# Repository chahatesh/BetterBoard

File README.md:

# BetterBoard

BetterBoard is a custom PCB I designed in KiCad. This repo contains the PCB design, schematics, and manufacturing files.

Betterboard is designed to operate efficiently on battery power and includes several debug LEDs. I created it because many of my projects rely on batteries, and troubleshooting them is often a major pain.

## USB Data Line Problem

One problem I ran into was routing the USB D+ and D- data lines. The connections crossed, which made it tricky to route the traces without interfering with each other.

## Finished PCB Design

After working through the routing issues, I finished the PCB layout. Here's the final design in KiCad.

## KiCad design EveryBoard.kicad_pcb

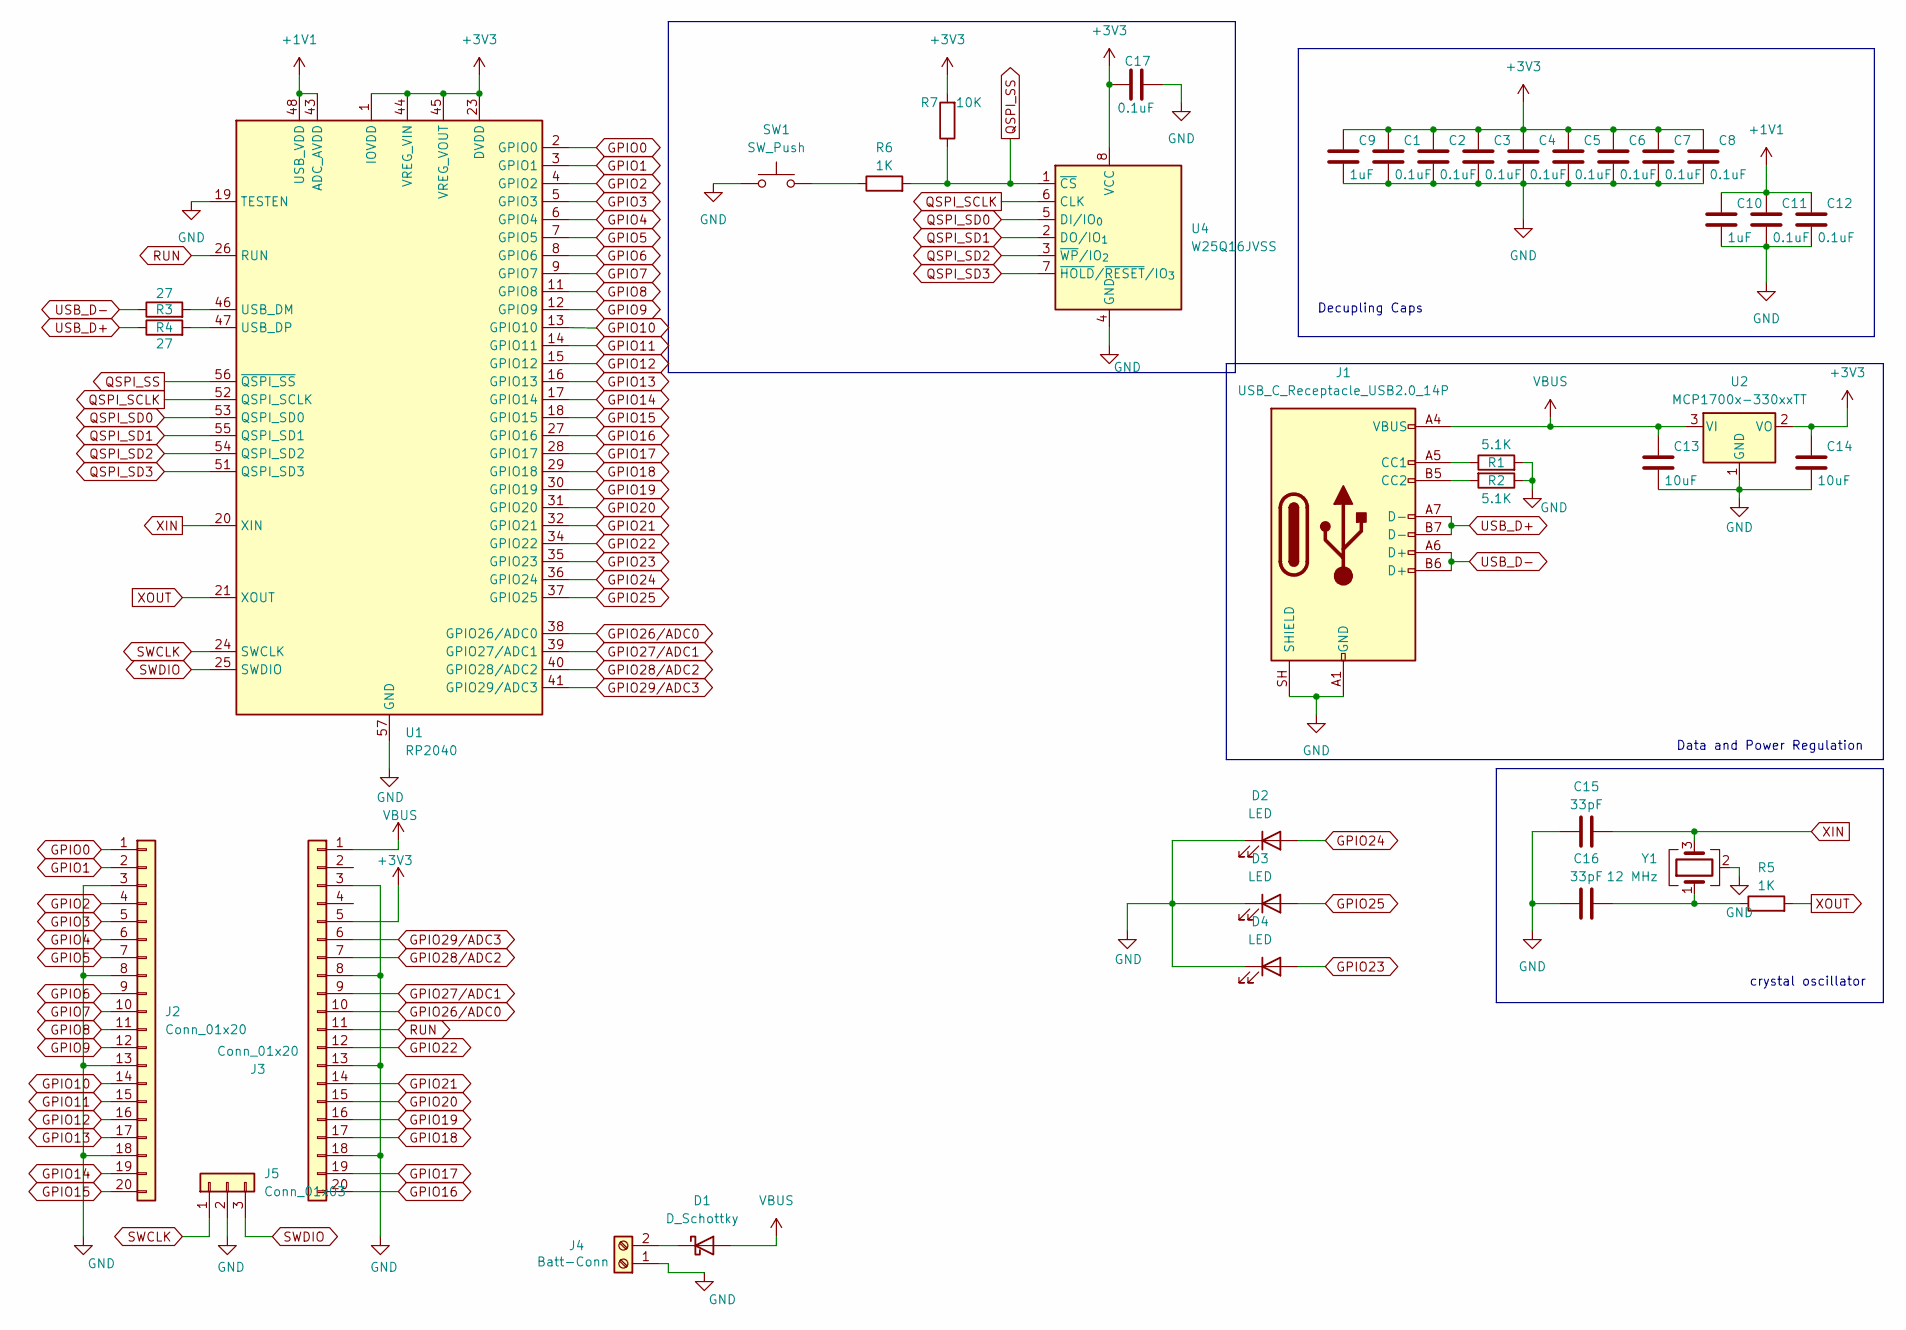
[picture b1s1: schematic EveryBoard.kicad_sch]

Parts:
C1, C2, C3, C4, C5, C6, C7, C8, C11, C12, C17: 0.1uF; C_0402_1005Metric
C9, C10: 1uF; C_0402_1005Metric
C13, C14: 10uF; C_0603_1608Metric
C15, C16: 33pF; C_0402_1005Metric
D1: D_Schottky; D_SOD-123
D2, D3, D4: LED; LED_0603_1608Metric
J1: USB_C_Receptacle_USB2.0_14P; USB_C_Receptacle_HRO_TYPE-C-31-M-12
J2, J3: Conn_01x20; PinHeader_1x20_P2.54mm_Vertical
J4: Batt-Conn; PinSocket_1x02_P2.54mm_Vertical
J5: Conn_01x03; PinHeader_1x03_P2.54mm_Vertical
R1, R2: 5.1K; R_0402_1005Metric
R3, R4: 27; R_0402_1005Metric
R5, R6: 1K; R_0402_1005Metric
R7: 10K; R_0402_1005Metric
SW1: SW_Push; SW_Push_SPST_NO_Alps_SKRK
U1: RP2040; QFN-56-1EP_7x7mm_P0.4mm_EP3.2x3.2mm
U2: MCP1700x-330xxTT; SOT-23
U4: W25Q16JVSS; Winbond_USON-8-1EP_3x2mm_P0.5mm_EP0.2x1.6mm
Y1: 12 MHz; Crystal_SMD_3225-4Pin_3.2x2.5mm

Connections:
+1V1: C10.1, C11.1, C12.1, U1.43 (ADC_AVDD), U1.48 (USB_VDD)
+3V3: C1.1, C2.1, C3.1, C4.1, C5.1, C6.1, C7.1, C8.1, C9.1, C14.1, C17.2, J3.5, R7.2, U1.1 (IOVDD), U1.10 (IOVDD), U1.22 (IOVDD), U1.23 (DVDD), U1.33 (IOVDD), U1.42 (IOVDD), U1.44 (VREG_VIN), U1.45 (VREG_VOUT), U1.49 (IOVDD), U1.50 (DVDD), U2.2 (VO), U4.8 (VCC)
GND: C1.2, C2.2, C3.2, C4.2, C5.2, C6.2, C7.2, C8.2, C9.2, C10.2, C11.2, C12.2, C13.2, C14.2, C15.1, C16.1, C17.1, D2.1 (K), D3.1 (K), D4.1 (K), J1.A1 (GND), J1.A12 (GND), J1.B1 (GND), J1.B12 (GND), J1.SH (SHIELD), J2.3, J2.8, J2.13, J2.18, J3.3, J3.8, J3.13, J3.18, J4.1, J5.2, R1.2, R2.1, SW1.1, U1.19 (TESTEN), U1.57 (GND), U2.1 (GND), U4.4 (GND), Y1.2 (G), Y1.4 (G)
GPIO0: J2.1, U1.2 (GPIO0)
GPIO1: J2.2, U1.3 (GPIO1)
GPIO2: J2.4, U1.4 (GPIO2)
GPIO3: J2.5, U1.5 (GPIO3)
GPIO4: J2.6, U1.6 (GPIO4)
GPIO5: J2.7, U1.7 (GPIO5)
GPIO6: J2.9, U1.8 (GPIO6)
GPIO7: J2.10, U1.9 (GPIO7)
GPIO8: J2.11, U1.11 (GPIO8)
GPIO9: J2.12, U1.12 (GPIO9)
GPIO10: J2.14, U1.13 (GPIO10)
GPIO11: J2.15, U1.14 (GPIO11)
GPIO12: J2.16, U1.15 (GPIO12)
GPIO13: J2.17, U1.16 (GPIO13)
GPIO14: J2.19, U1.17 (GPIO14)
GPIO15: J2.20, U1.18 (GPIO15)
GPIO16: J3.20, U1.27 (GPIO16)
GPIO17: J3.19, U1.28 (GPIO17)
GPIO18: J3.17, U1.29 (GPIO18)
GPIO19: J3.16, U1.30 (GPIO19)
GPIO20: J3.15, U1.31 (GPIO20)
GPIO21: J3.14, U1.32 (GPIO21)
GPIO22: J3.12, U1.34 (GPIO22)
GPIO23: D4.2 (A), U1.35 (GPIO23)
GPIO24: D2.2 (A), U1.36 (GPIO24)
GPIO25: D3.2 (A), U1.37 (GPIO25)
GPIO26/ADC0: J3.10, U1.38 (GPIO26/ADC0)
GPIO27/ADC1: J3.9, U1.39 (GPIO27/ADC1)
GPIO28/ADC2: J3.7, U1.40 (GPIO28/ADC2)
GPIO29/ADC3: J3.6, U1.41 (GPIO29/ADC3)
unnamed: C16.2, R5.1, Y1.1
unnamed: D1.1 (K), J4.2
unnamed: J1.A5 (CC1), R1.1
unnamed: J1.B5 (CC2), R2.2
unnamed: R6.1, SW1.2
unnamed: R3.2, U1.46 (USB_DM)
unnamed: R4.2, U1.47 (USB_DP)
QSPI_SCLK: U1.52 (QSPI_SCLK), U4.6 (CLK)
QSPI_SD0: U1.53 (QSPI_SD0), U4.5 (DI/IO_{0})
QSPI_SD1: U1.55 (QSPI_SD1), U4.2 (DO/IO_{1})
QSPI_SD2: U1.54 (QSPI_SD2), U4.3 (~WP/IO_{2})
QSPI_SD3: U1.51 (QSPI_SD3), U4.7 (~HOLD/~RESET/IO_{3})
QSPI_SS: R6.2, R7.1, U1.56 (~QSPI_SS), U4.1 (~CS)
RUN: J3.11, U1.26 (RUN)
SWCLK: J5.1, U1.24 (SWCLK)
SWDIO: J5.3, U1.25 (SWDIO)
USB_D+: J1.A7 (D-), J1.B7 (D-), R4.1
USB_D-: J1.A6 (D+), J1.B6 (D+), R3.1
VBUS: C13.1, D1.2 (A), J1.A4 (VBUS), J1.A9 (VBUS), J1.B4 (VBUS), J1.B9 (VBUS), J3.1, U2.3 (VI)
XIN: C15.2, U1.20 (XIN), Y1.3
XOUT: R5.2, U1.21 (XOUT)

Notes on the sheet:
Decupling Caps
crystal oscillator
Data and Power Regulation

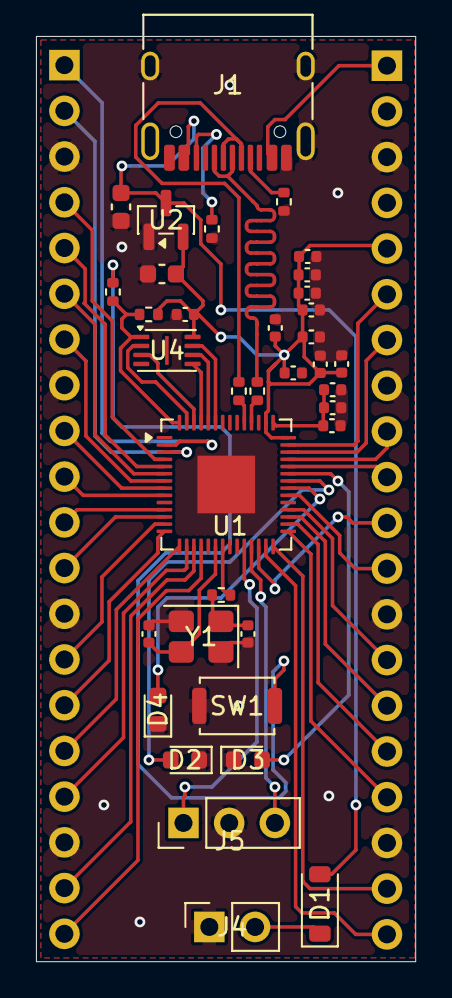
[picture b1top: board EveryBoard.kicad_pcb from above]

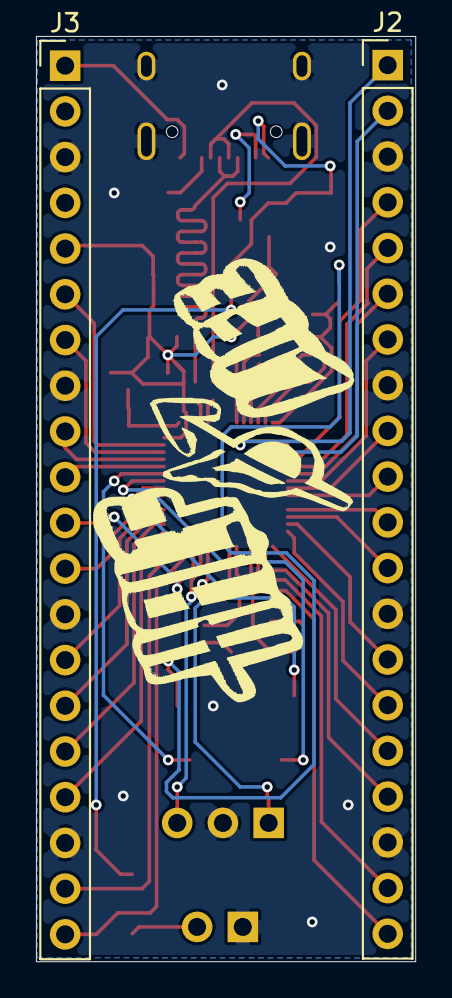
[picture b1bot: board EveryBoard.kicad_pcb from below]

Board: 2 copper layers, 21.1 x 51.4 mm, 38 parts (2 on the bottom side), 54 nets.
